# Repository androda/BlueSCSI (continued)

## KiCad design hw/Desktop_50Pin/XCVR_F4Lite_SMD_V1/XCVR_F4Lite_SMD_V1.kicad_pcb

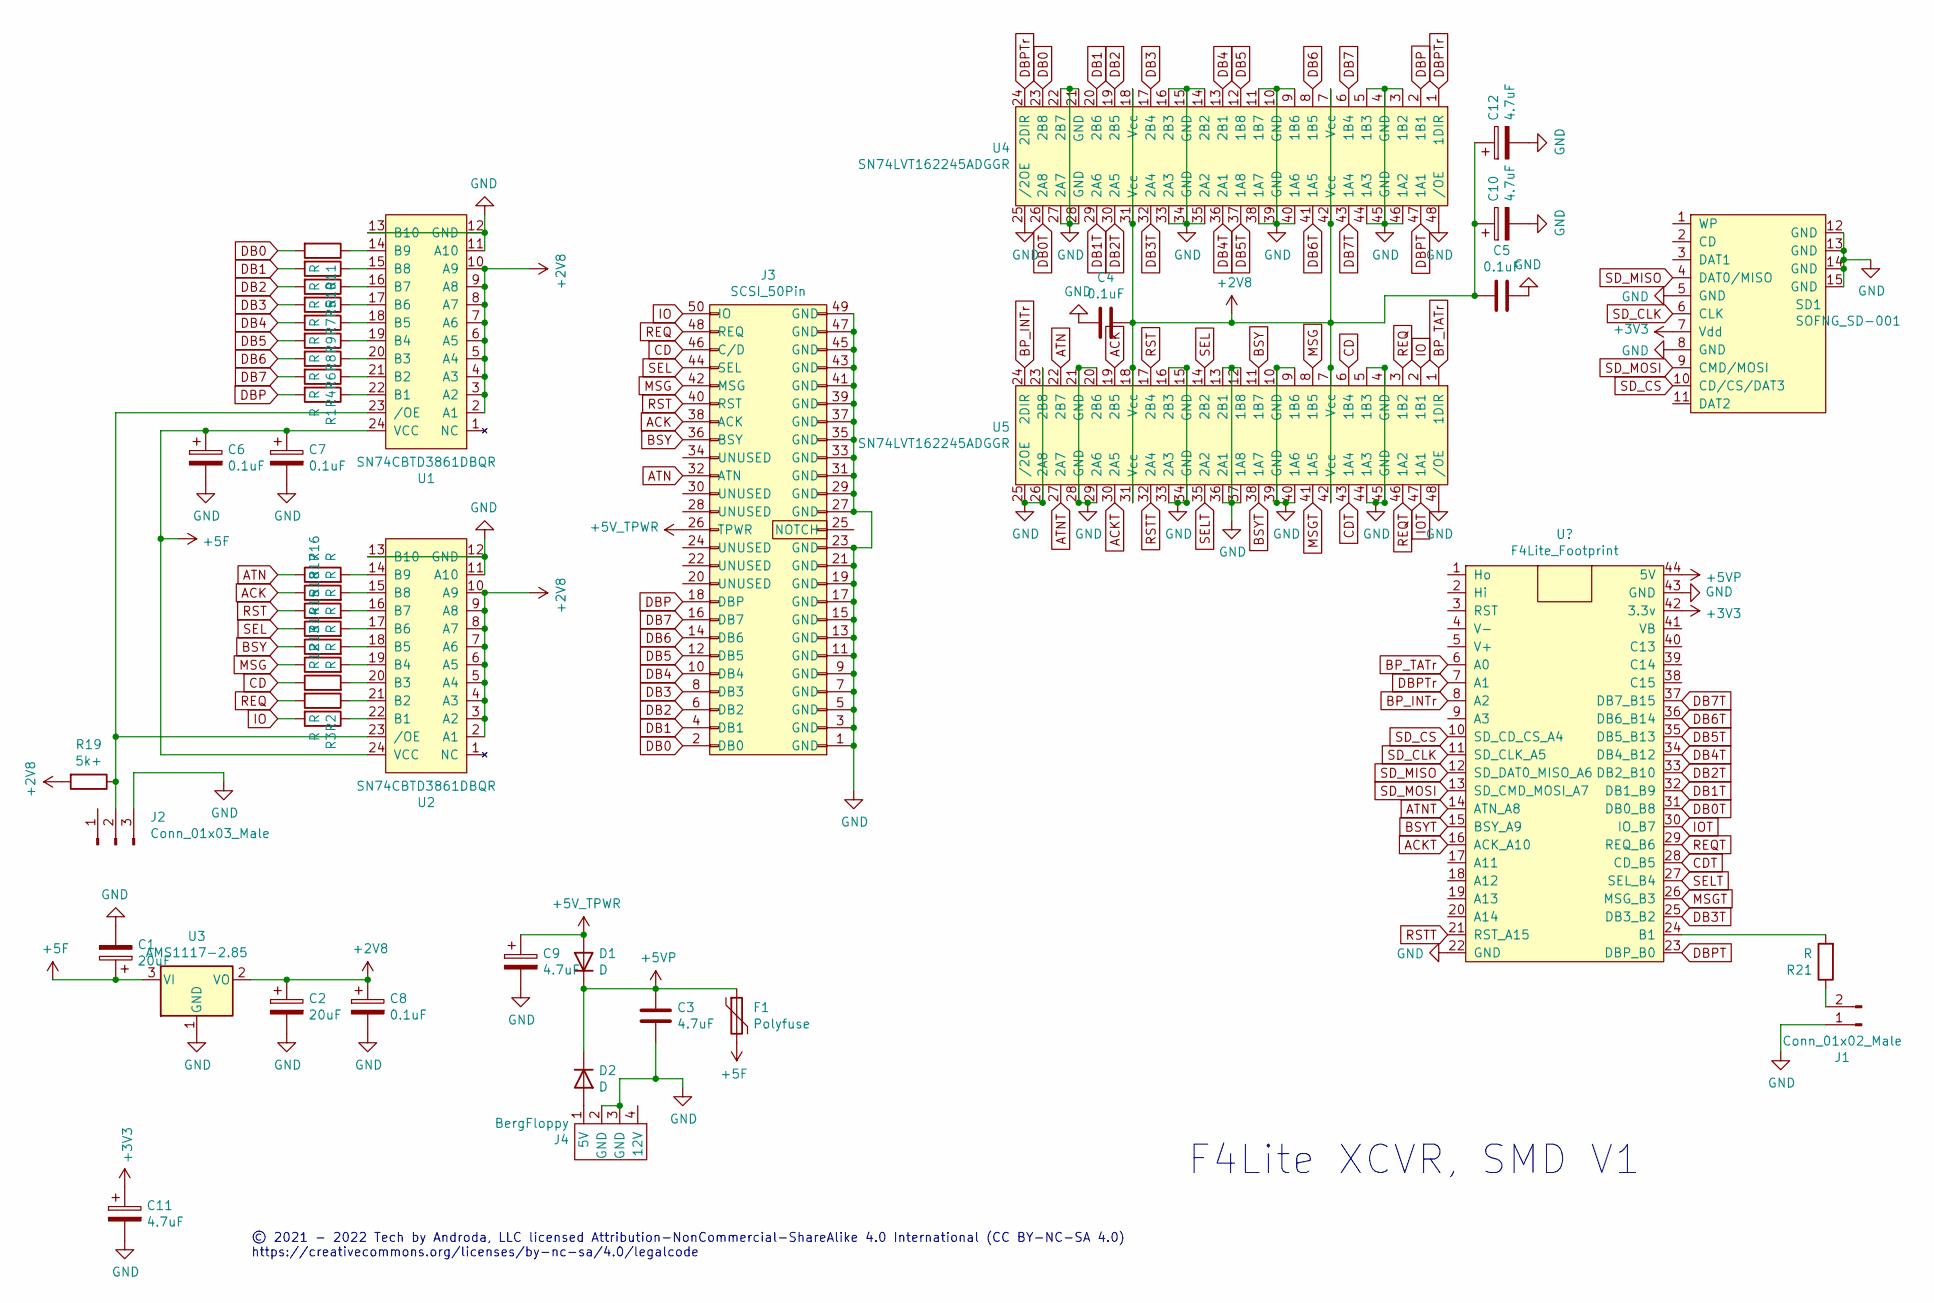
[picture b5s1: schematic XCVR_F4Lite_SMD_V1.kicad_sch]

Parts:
C1, C2: 20uF; C_1206_3216Metric_Pad1.42x1.75mm_HandSolder
C3, C9, C10, C11, C12: 4.7uF; C_0805_2012Metric_Pad1.15x1.40mm_HandSolder
C4, C5, C6, C7, C8: 0.1uF; C_0805_2012Metric_Pad1.15x1.40mm_HandSolder
D1, D2: D; D_SMA
F1: Polyfuse; Fuse_BelFuse_0ZRE0005FF_L8.3mm_W3.8mm
J1: Conn_01x02_Male; PinHeader_1x02_P2.54mm_Vertical
J2: Conn_01x03_Male; PinHeader_1x03_P2.54mm_Vertical
J3: SCSI_50Pin; SCSI50_EdgeConn
J4: BergFloppy; BergFloppy_RightAngle
R1, R2, R3, R4, R5, R6, R7, R8, R9, R10, R11, R12, R13, R14, R15, R16, R17, R18: R; R_0603_1608Metric_Pad1.05x0.95mm_HandSolder
R19: 5k+; R_0805_2012Metric_Pad1.15x1.40mm_HandSolder
R21: R; R_0805_2012Metric_Pad1.15x1.40mm_HandSolder
SD1: SOFNG_SD-001
U1, U2: SN74CBTD3861DBQR; SSOP-24_3.9x8.7mm_P0.635mm
U3: AMS1117-2.85; SOT-223-3_TabPin2
U4, U5: SN74LVT162245ADGGR; TSSOP-48_6.1x12.5mm_P0.5mm

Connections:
+2V8: C2.1, C4.1, C5.1, C8.1, C10.1, C12.1, R19.2, U1.2 (A1), U1.3 (A2), U1.4 (A3), U1.5 (A4), U1.6 (A5), U1.7 (A6), U1.8 (A7), U1.9 (A8), U1.10 (A9), U2.2 (A1), U2.3 (A2), U2.4 (A3), U2.5 (A4), U2.6 (A5), U2.7 (A6), U2.8 (A7), U2.9 (A8), U2.10 (A9), U3.2 (VO), U4.7 (Vcc), U4.18 (Vcc), U4.31 (Vcc), U4.42 (Vcc), U5.7 (Vcc), U5.18 (Vcc), U5.31 (Vcc), U5.42 (Vcc)
+3V3: C11.1, SD1.7 (Vdd); also elsewhere on the board
+5F: C1.1, C6.1, C7.1, F1.2, U1.24 (VCC), U2.24 (VCC), U3.3 (VI)
+5V: C9.1, D1.2 (A), J3.26 (TPWR)
+5VP: C3.1, D1.1 (K), D2.1 (K), F1.1; also elsewhere on the board
ACK: J3.38 (ACK), R17.1, U5.19 (2B5)
ACKT: U5.30 (2A5); also elsewhere on the board
ATN: J3.32 (ATN), R16.1, U5.22 (2B7)
ATNT: U5.27 (2A7); also elsewhere on the board
BP_INTr: U5.24 (2DIR); also elsewhere on the board
BP_TATr: U5.1 (1DIR); also elsewhere on the board
BSY: J3.36 (BSY), R14.1, U5.11 (1B7)
BSYT: U5.38 (1A7); also elsewhere on the board
CD: J3.46 (C/D), R12.1, U5.6 (1B4)
CDT: U5.43 (1A4); also elsewhere on the board
DB0: J3.2 (DB0), R11.2, U4.23 (2B8)
DB0T: U4.26 (2A8); also elsewhere on the board
DB1: J3.4 (DB1), R10.2, U4.20 (2B6)
DB1T: U4.29 (2A6); also elsewhere on the board
DB2: J3.6 (DB2), R5.2, U4.19 (2B5)
DB2T: U4.30 (2A5); also elsewhere on the board
DB3: J3.8 (DB3), R7.2, U4.17 (2B4)
DB3T: U4.32 (2A4); also elsewhere on the board
DB4: J3.10 (DB4), R9.2, U4.13 (2B1)
DB4T: U4.36 (2A1); also elsewhere on the board
DB5: J3.12 (DB5), R8.2, U4.12 (1B8)
DB5T: U4.37 (1A8); also elsewhere on the board
DB6: J3.14 (DB6), R6.2, U4.8 (1B5)
DB6T: U4.41 (1A5); also elsewhere on the board
DB7: J3.16 (DB7), R4.2, U4.6 (1B4)
DB7T: U4.43 (1A4); also elsewhere on the board
DBP: J3.18 (DBP), R1.2, U4.2 (1B1)
DBPT: U4.47 (1A1); also elsewhere on the board
DBPTr: U4.1 (1DIR), U4.24 (2DIR); also elsewhere on the board
GND: C1.2, C2.2, C3.2, C4.2, C5.2, C6.2, C7.2, C8.2, C9.2, C10.2, C11.2, C12.2, J1.1, J2.3, J3.1 (GND), J3.3 (GND), J3.5 (GND), J3.7 (GND), J3.9 (GND), J3.11 (GND), J3.13 (GND), J3.15 (GND), J3.17 (GND), J3.19 (GND), J3.21 (GND), J3.23 (GND), J3.27 (GND), J3.29 (GND), J3.31 (GND), J3.33 (GND), J3.35 (GND), J3.37 (GND), J3.39 (GND), J3.41 (GND), J3.43 (GND), J3.45 (GND), J3.47 (GND), J3.49 (GND), J4.2 (GND), J4.3 (GND), SD1.5 (GND), SD1.8 (GND), SD1.12 (GND), SD1.13 (GND), SD1.14 (GND), SD1.15 (GND), U1.11 (A10), U1.12 (GND), U1.13 (B10), U2.11 (A10), U2.12 (GND), U2.13 (B10), U3.1 (GND), U4.3 (1B2), U4.4 (GND), U4.5 (1B3), U4.9 (1B6), U4.10 (GND), U4.11 (1B7), U4.14 (2B2), U4.15 (GND), U4.16 (2B3), U4.21 (GND), U4.22 (2B7), U4.25 (/2OE), U4.27 (2A7), U4.28 (GND), U4.33 (2A3), U4.34 (GND), U4.35 (2A2), U4.38 (1A7), U4.39 (GND), U4.40 (1A6), U4.44 (1A3), U4.45 (GND), U4.46 (1A2), U4.48 (/OE), U5.4 (GND), U5.5 (1B3), U5.9 (1B6), U5.10 (GND), U5.12 (1B8), U5.13 (2B1), U5.15 (GND), U5.16 (2B3), U5.20 (2B6), U5.21 (GND), U5.23 (2B8), U5.25 (/2OE), U5.26 (2A8), U5.28 (GND), U5.29 (2A6), U5.33 (2A3), U5.34 (GND), U5.36 (2A1), U5.37 (1A8), U5.39 (GND), U5.40 (1A6), U5.44 (1A3), U5.45 (GND), U5.48 (/OE); also elsewhere on the board
IO: J3.50 (IO), R3.2, U5.2 (1B1)
IOT: U5.47 (1A1); also elsewhere on the board
MSG: J3.42 (MSG), R13.1, U5.8 (1B5)
MSGT: U5.41 (1A5); also elsewhere on the board
unnamed: D2.2 (A), J4.1 (5V)
unnamed: J1.2, R21.1
unnamed: J2.2, R19.1, U1.23 (/OE), U2.23 (/OE)
unnamed: R1.1, U1.22 (B1)
unnamed: R2.1, U2.21 (B2)
unnamed: R3.1, U2.22 (B1)
unnamed: R4.1, U1.21 (B2)
unnamed: R5.1, U1.16 (B7)
unnamed: R6.1, U1.20 (B3)
unnamed: R7.1, U1.17 (B6)
unnamed: R8.1, U1.19 (B4)
unnamed: R9.1, U1.18 (B5)
unnamed: R10.1, U1.15 (B8)
unnamed: R11.1, U1.14 (B9)
unnamed: R12.2, U2.20 (B3)
unnamed: R13.2, U2.19 (B4)
unnamed: R14.2, U2.18 (B5)
unnamed: R15.2, U2.17 (B6)
unnamed: R16.2, U2.14 (B9)
unnamed: R17.2, U2.15 (B8)
unnamed: R18.2, U2.16 (B7)
unnamed 69: R21.2; also elsewhere on the board
REQ: J3.48 (REQ), R2.2, U5.3 (1B2)
REQT: U5.46 (1A2); also elsewhere on the board
RST: J3.40 (RST), R18.1, U5.17 (2B4)
RSTT: U5.32 (2A4); also elsewhere on the board
SD_CLK: SD1.6 (CLK); also elsewhere on the board
SD_CS: SD1.10 (CD/CS/DAT3); also elsewhere on the board
SD_MISO: SD1.4 (DAT0/MISO); also elsewhere on the board
SD_MOSI: SD1.9 (CMD/MOSI); also elsewhere on the board
SEL: J3.44 (SEL), R15.1, U5.14 (2B2)
SELT: U5.35 (2A2); also elsewhere on the board

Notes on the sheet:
© 2021 - 2022 Tech by Androda, LLC licensed Attribution-NonCommercial-ShareAlike 4.0 International (CC BY-NC-SA 4.0) https://creativecommons.org/licenses/by-nc-sa/4.0/legalcode
F4Lite XCVR, SMD V1

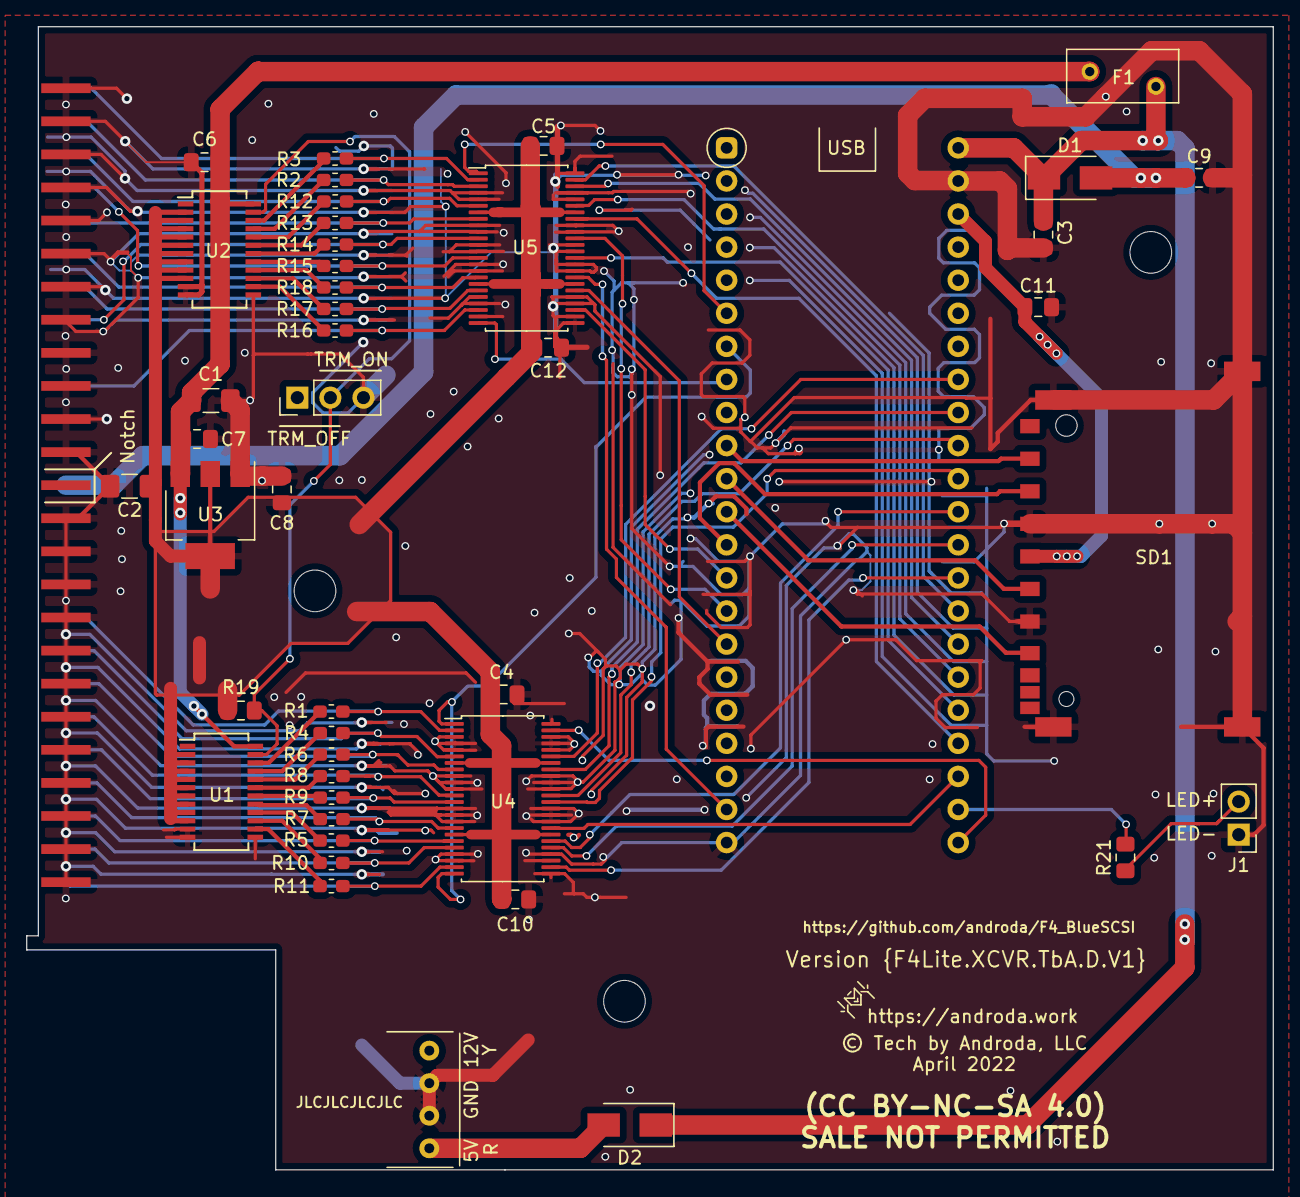
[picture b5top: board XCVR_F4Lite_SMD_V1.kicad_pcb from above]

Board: 2 copper layers, 95.7 x 87.8 mm, 46 parts (0 on the bottom side), 71 nets.

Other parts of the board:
U6: GreenSCSI_F401

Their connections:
+3V3: U6.42; also elsewhere on the board
+5VP: U6.44; also elsewhere on the board
ACKT: U6.16; also elsewhere on the board
ATNT: U6.14; also elsewhere on the board
BP_INTr: U6.8; also elsewhere on the board
BP_TATr: U6.6; also elsewhere on the board
BSYT: U6.15; also elsewhere on the board
CDT: U6.28; also elsewhere on the board
DB0T: U6.31; also elsewhere on the board
DB1T: U6.32; also elsewhere on the board
DB2T: U6.33; also elsewhere on the board
DB3T: U6.25; also elsewhere on the board
DB4T: U6.34; also elsewhere on the board
DB5T: U6.35; also elsewhere on the board
DB6T: U6.36; also elsewhere on the board
DB7T: U6.37; also elsewhere on the board
DBPT: U6.23; also elsewhere on the board
DBPTr: U6.7; also elsewhere on the board
GND: U6.22, U6.43; also elsewhere on the board
IOT: U6.30; also elsewhere on the board
MSGT: U6.26; also elsewhere on the board
unnamed 69: U6.24; also elsewhere on the board
REQT: U6.29; also elsewhere on the board
RSTT: U6.21; also elsewhere on the board
SD_CLK: U6.11; also elsewhere on the board
SD_CS: U6.10; also elsewhere on the board
SD_MISO: U6.12; also elsewhere on the board
SD_MOSI: U6.13; also elsewhere on the board
SELT: U6.27; also elsewhere on the board

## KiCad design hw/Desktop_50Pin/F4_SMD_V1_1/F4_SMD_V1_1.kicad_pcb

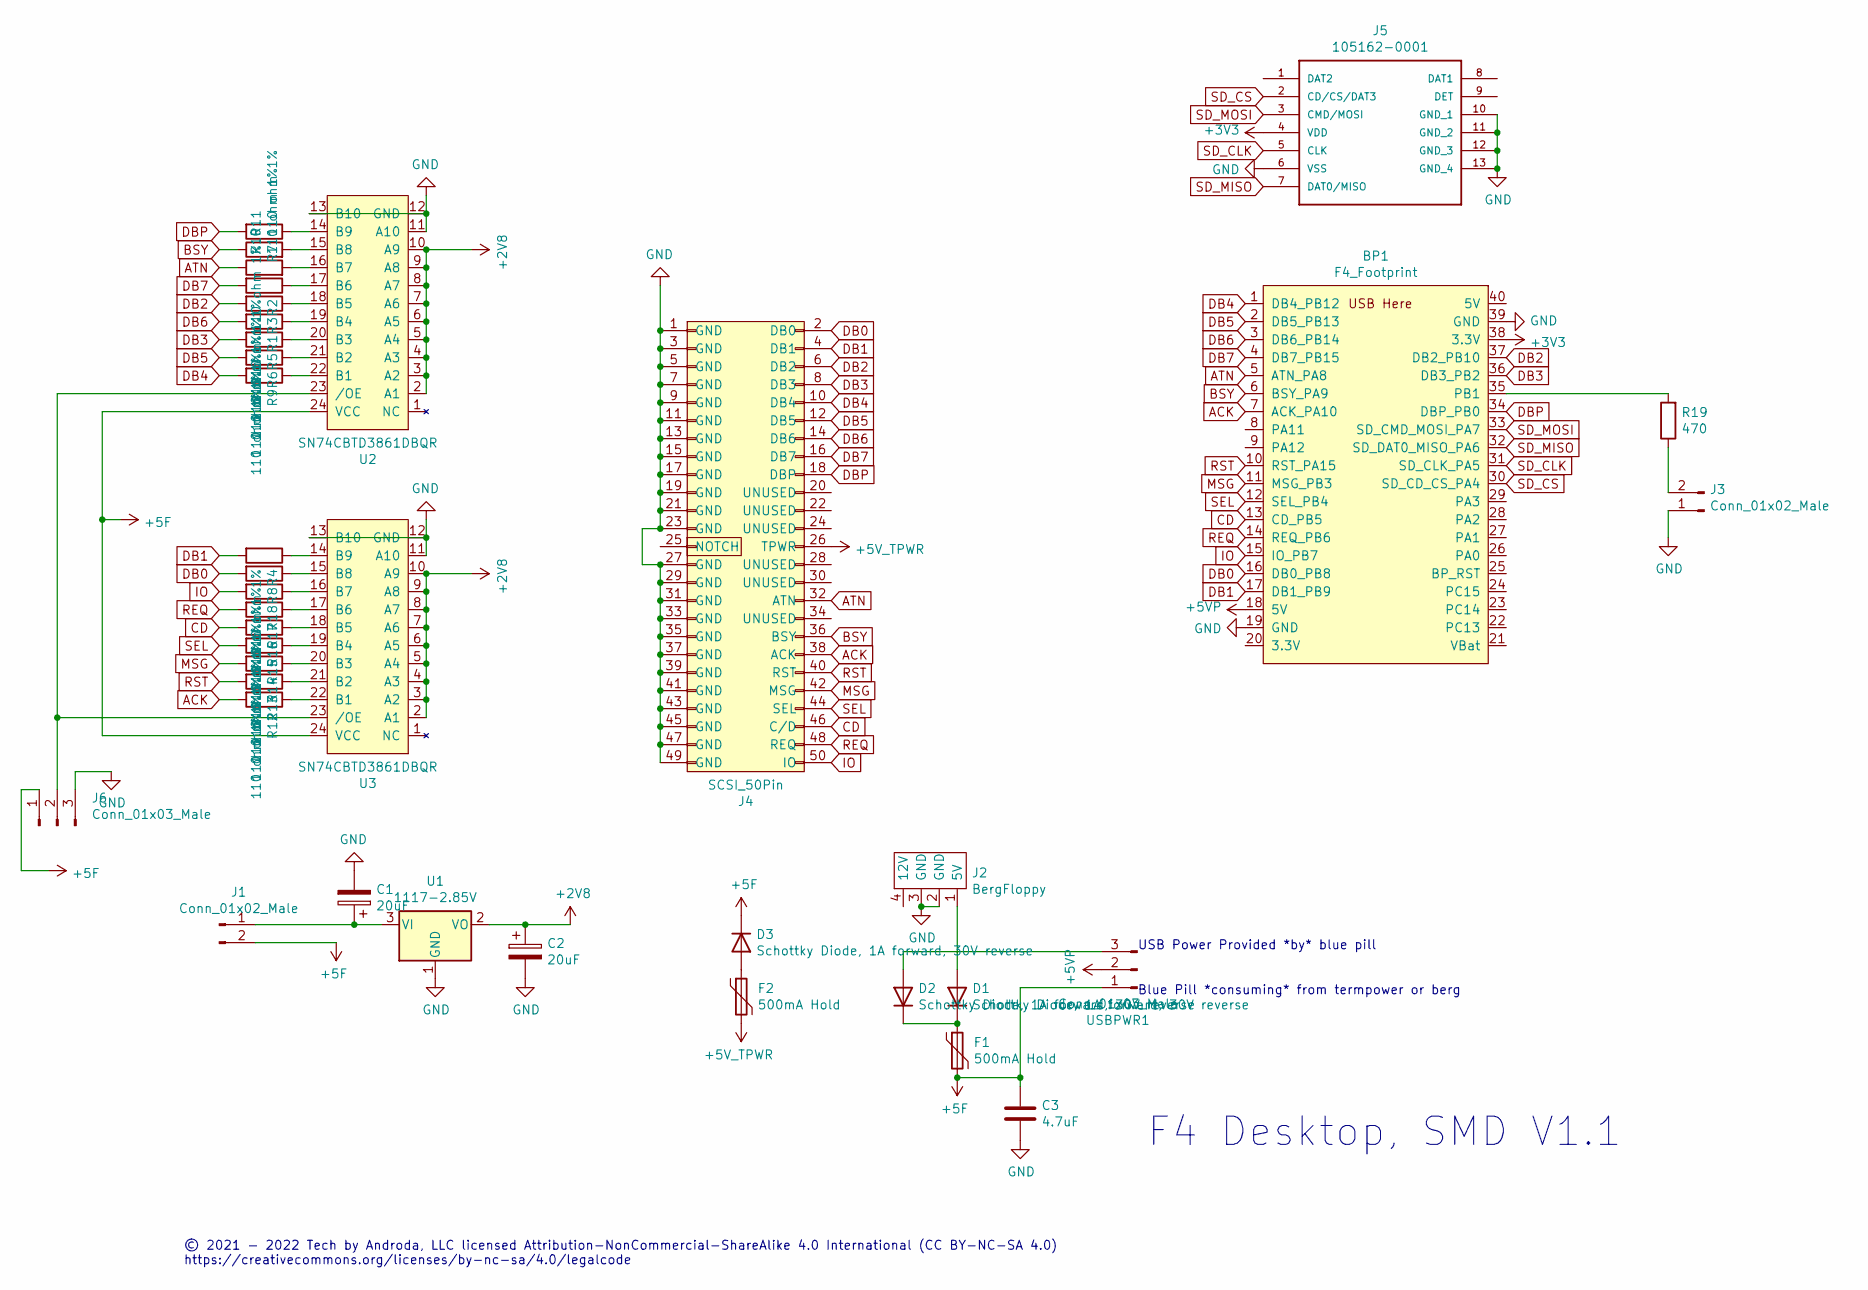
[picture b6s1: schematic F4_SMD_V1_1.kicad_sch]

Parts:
BP1: F4_Footprint; BluePillModule
C1, C2: 20uF; C_1206_3216Metric_Pad1.42x1.75mm_HandSolder
C3: 4.7uF; C_0805_2012Metric_Pad1.15x1.40mm_HandSolder
D1, D2, D3: Schottky Diode, 1A forward, 30V reverse; D_SOD-123F
F1, F2: 500mA Hold; Fuse_0805_2012Metric_Castellated
J1, J3: Conn_01x02_Male; PinHeader_1x02_P2.54mm_Vertical
J2: BergFloppy; BergFloppy_RightAngle
J4: SCSI_50Pin; SCSI_Internal_50Pin
J5: 105162-0001; microsd_molex_1051620001; MANUFACTURER_PART_NUMBER 105162-0001; MOUSER_PART_NUMBER 538-105162-0001
J6: Conn_01x03_Male; PinHeader_1x03_P2.54mm_Vertical
R1, R2, R3, R4, R5, R6, R7, R8, R9, R10, R11, R12, R13, R14, R15, R16, R17, R18: 110 ohm 1%; R_0603_1608Metric_Pad1.05x0.95mm_HandSolder
R19: 470; R_Axial_DIN0207_L6.3mm_D2.5mm_P7.62mm_Horizontal
U1: 1117-2.85V; SOT-223-3_TabPin2
U2, U3: SN74CBTD3861DBQR; SSOP-24_3.9x8.7mm_P0.635mm
USBPWR1: Conn_01x03_Male; PinHeader_1x03_P2.54mm_Vertical

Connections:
+2V8: C2.1, U1.2 (VO), U2.2 (A1), U2.3 (A2), U2.4 (A3), U2.5 (A4), U2.6 (A5), U2.7 (A6), U2.8 (A7), U2.9 (A8), U2.10 (A9), U3.2 (A1), U3.3 (A2), U3.4 (A3), U3.5 (A4), U3.6 (A5), U3.7 (A6), U3.8 (A7), U3.9 (A8), U3.10 (A9)
+3V3: BP1.38 (3.3V), J5.4 (VDD)
+5F: C3.1, D3.1 (K), F1.2, J1.2, J6.1, U2.24 (VCC), U3.24 (VCC), USBPWR1.1; also elsewhere on the board
+5V: F2.2, J4.26 (TPWR)
+5VP: BP1.18 (5V), USBPWR1.2; also elsewhere on the board
ACK: BP1.7 (ACK_PA10), J4.38 (ACK), R12.2
ATN: BP1.5 (ATN_PA8), J4.32 (ATN), R10.1
BSY: BP1.6 (BSY_PA9), J4.36 (BSY), R11.1
CD: BP1.13 (CD_PB5), J4.46 (C/D), R16.2
DB0: BP1.16 (DB0_PB8), J4.2 (DB0), R8.2
DB1: BP1.17 (DB1_PB9), J4.4 (DB1), R4.2
DB2: BP1.37 (DB2_PB10), J4.6 (DB2), R3.2
DB3: BP1.36 (DB3_PB2), J4.8 (DB3), R5.2
DB4: BP1.1 (DB4_PB12), J4.10 (DB4), R9.2
DB5: BP1.2 (DB5_PB13), J4.12 (DB5), R6.2
DB6: BP1.3 (DB6_PB14), J4.14 (DB6), R1.2
DB7: BP1.4 (DB7_PB15), J4.16 (DB7), R2.2
DBP: BP1.34 (DBP_PB0), J4.18 (DBP), R7.2
GND: BP1.19 (GND), BP1.39 (GND), C1.2, C2.2, C3.2, J2.2 (GND), J2.3 (GND), J3.1, J4.1 (GND), J4.3 (GND), J4.5 (GND), J4.7 (GND), J4.9 (GND), J4.11 (GND), J4.13 (GND), J4.15 (GND), J4.17 (GND), J4.19 (GND), J4.21 (GND), J4.23 (GND), J4.27 (GND), J4.29 (GND), J4.31 (GND), J4.33 (GND), J4.35 (GND), J4.37 (GND), J4.39 (GND), J4.41 (GND), J4.43 (GND), J4.45 (GND), J4.47 (GND), J4.49 (GND), J5.6 (VSS), J5.10 (GND_1), J5.11 (GND_2), J5.12 (GND_3), J5.13 (GND_4), J6.3, U1.1 (GND), U2.11 (A10), U2.12 (GND), U2.13 (B10), U3.11 (A10), U3.12 (GND), U3.13 (B10)
IO: BP1.15 (IO_PB7), J4.50 (IO), R18.2
MSG: BP1.11 (MSG_PB3), J4.42 (MSG), R14.2
unnamed: BP1.35 (PB1), R19.2
unnamed: C1.1, J1.1, U1.3 (VI)
unnamed: D1.1 (K), D2.1 (K), F1.1
unnamed: D1.2 (A), J2.1 (5V)
unnamed 25: D2.2 (A), USBPWR1.3; also elsewhere on the board
unnamed: D3.2 (A), F2.1
unnamed: J3.2, R19.1
unnamed: J6.2, U2.23 (/OE), U3.23 (/OE)
unnamed: R1.1, U2.19 (B4)
unnamed: R2.1, U2.17 (B6)
unnamed: R3.1, U2.18 (B5)
unnamed: R4.1, U3.14 (B9)
unnamed: R5.1, U2.20 (B3)
unnamed: R6.1, U2.21 (B2)
unnamed: R7.1, U2.14 (B9)
unnamed: R8.1, U3.15 (B8)
unnamed: R9.1, U2.22 (B1)
unnamed: R10.2, U2.16 (B7)
unnamed: R11.2, U2.15 (B8)
unnamed: R12.1, U3.22 (B1)
unnamed: R13.1, U3.21 (B2)
unnamed: R14.1, U3.20 (B3)
unnamed: R15.1, U3.19 (B4)
unnamed: R16.1, U3.18 (B5)
unnamed: R17.1, U3.17 (B6)
unnamed: R18.1, U3.16 (B7)
REQ: BP1.14 (REQ_PB6), J4.48 (REQ), R17.2
RST: BP1.10 (RST_PA15), J4.40 (RST), R13.2
SD_CLK: BP1.31 (SD_CLK_PA5), J5.5 (CLK)
SD_CS: BP1.30 (SD_CD_CS_PA4), J5.2 (CD/CS/DAT3)
SD_MISO: BP1.32 (SD_DAT0_MISO_PA6), J5.7 (DAT0/MISO)
SD_MOSI: BP1.33 (SD_CMD_MOSI_PA7), J5.3 (CMD/MOSI)
SEL: BP1.12 (SEL_PB4), J4.44 (SEL), R15.2

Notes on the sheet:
© 2021 - 2022 Tech by Androda, LLC licensed Attribution-NonCommercial-ShareAlike 4.0 International (CC BY-NC-SA 4.0) https://creativecommons.org/licenses/by-nc-sa/4.0/legalcode
F4 Desktop, SMD V1.1
Blue Pill *consuming* from termpower or berg
USB Power Provided *by* blue pill

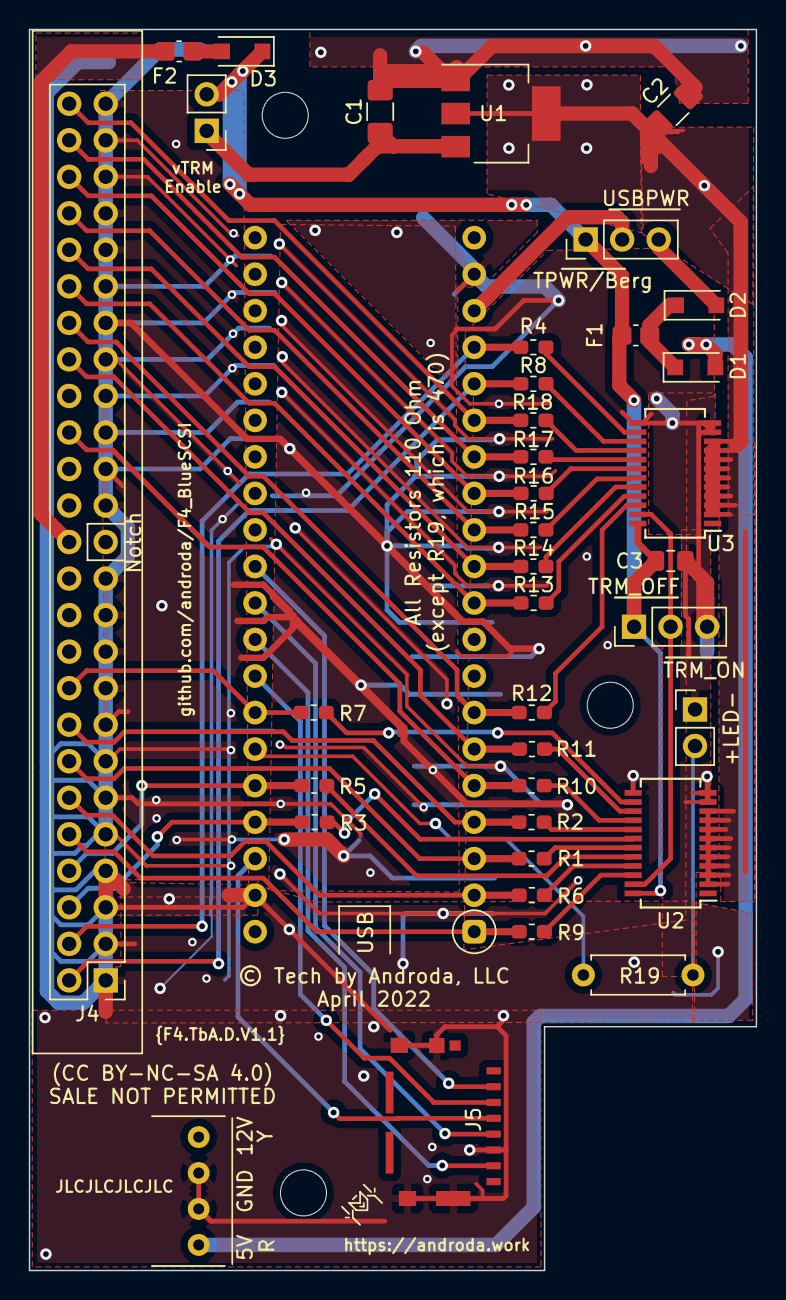
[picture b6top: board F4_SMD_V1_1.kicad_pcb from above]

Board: 2 copper layers, 50.5 x 86.3 mm, 38 parts (0 on the bottom side), 54 nets.

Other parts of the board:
USBPWR: Conn_01x03_Male; PinHeader_1x03_P2.54mm_Vertical

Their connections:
+5F: USBPWR.1; also elsewhere on the board
+5VP: USBPWR.2; also elsewhere on the board
unnamed 25: USBPWR.3; also elsewhere on the board

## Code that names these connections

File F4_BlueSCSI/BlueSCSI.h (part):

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//#define DB5       PB13    // SCSI:DB5
//#define DB6       PB14    // SCSI:DB6
//#define DB7       PB15    // SCSI:DB7
//#define DBP       PB0     // SCSI:DBP

#define ATN       PA8      // SCSI:ATN
#define BSY       PA9      // SCSI:BSY
#define ACK       PA10     // SCSI:ACK
#define RST       PA15     // SCSI:RST
#define MSG       PB3      // SCSI:MSG
#define SEL       PB4      // SCSI:SEL
#define CD        PB5      // SCSI:C/D
#define REQ       PB6      // SCSI:REQ
#define IO        PB7      // SCSI:I/O

#define LED       PC13     // LED
#define LED2      PB1      // Driven LED

// Image Set Selector
#define IMAGE_SELECT1   PC14
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#define GPIOREG(VPIN)     ((VPIN) >= 16 ? PBREG : PAREG)
#define BITMASK(VPIN)     (1 << ((VPIN) & 15))

#define vATN       PA(8)      // SCSI:ATN
#define vBSY       PA(9)      // SCSI:BSY
#define vACK       PA(10)     // SCSI:ACK
#define vRST       PA(15)     // SCSI:RST
#define vMSG       PB(3)      // SCSI:MSG
#define vSEL       PB(4)      // SCSI:SEL
#define vCD        PB(5)      // SCSI:C/D
#define vREQ       PB(6)      // SCSI:REQ
#define vIO        PB(7)      // SCSI:I/O
#define vSD_CS     PA(4)      // SDCARD:CS

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#else

// Turn on the output only for BSY
#define SCSI_BSY_ACTIVE()      { pinMode(BSY, OUTPUT_OPEN_DRAIN); SCSI_OUT(vBSY,  active) }

// BSY,REQ,MSG,CD,IO Turn off output, BSY is the last input
#define SCSI_TARGET_INACTIVE() { SCSI_OUT(vREQ,inactive); SCSI_PHASE_CHANGE(SCSI_PHASE_DATAOUT); SCSI_OUT(vBSY,inactive); pinMode(BSY, INPUT); }

// BSY,REQ,MSG,CD,IO Turn on the output (no change required for OD)
#define SCSI_TARGET_ACTIVE()   { }
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*/
/**
 * BSRR register generator
 * Totally configurable for which pin is each data bit, which pin is PTY, and which pin is REQ.
 * The only requirement is that data and parity pins are in the same GPIO block.
 * REQ can be specified as -1 to ignore, as it doesn't have to be in the same GPIO block.
 * This is dramatically slower than the original static array, but is easier to configure
 */
static uint32_t genBSRR(uint32_t data) {
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  }

  // BSRR set REQ if specified
  // Only set > 0 if it's in the same GPIO block as DB and DBP
  if (reqPosition >= 0) {
    output |= 0x01 << reqPosition;
  }
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
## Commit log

2021-11-11 Remove parent bluescsi files
2021-11-11 Move and rename, update readme
2021-11-11 Add to LICENSE
2022-02-22 Allow for 2048 block size
2022-02-22 Fix warnings
2022-02-22 Dont consider LUN in filename as it wont work, just force to 0
2022-02-22 Various fixes for VAXstation
2022-02-22 Fix indenting
2022-02-22 Minor white space fixes. Snapshot to VERSION
2022-03-05 Fighting with markdown
2022-03-05 Update README
    generally generally
2022-03-05 Update Readme
    Link to flashing firmware updates wiki page
2022-03-21 Add SGI Indy Benchmark Results
2022-04-06 Make documentation license a little clearer
2022-04-06 More docs license
    Maybe overboard to stick it everywhere, but why not?
2022-04-06 Build Instructions
    Not absolutely the clearest, but it's all laid out at least
2022-04-06 Doc tweaks
2022-04-06 Update Hardware License
2022-04-06 Hardware Release, in KiCAD V6 format
    CC BY-NC-SA 4.0 licensed hardware release.
    Note that these are all slightly tweaked versions of the ones currently for sale, and as such have not been produced for testing.
2022-04-07 Fix documentation flub
2022-04-07 Fix filename
    Not sure where this came from, that filename is from an ancient prototype
2022-04-07 Pointer to dev instructions folder
2022-04-07 CLZ optimization
2022-04-07 Optimize handling of reset interrupt.
2022-04-07 F4-specific fix for EXTI issues
2022-04-07 Add explicit "bx lr" to longjmpFromInterrupt.
2022-04-07 Move the db_bsrr table to RAM for faster performance.
2022-04-07 Separate out writeDataLoop. Adjust the timing, and incorporate the loop overhead in to one of the desired delays.
2022-04-07 Read timing adjustment, now getting 1216 KB/sec on LC III+. First pass at write speed optimization, now getting 825 KB/sec on LC III+. Whitespace cleanup.
2022-04-07 Pin down alignment for writeDataLoop and readDataLoop, and perform some additional timing adjustment.
2022-04-07 Switch to latest toolchain. Tune the timing for the readDataLoop with the latest toolchain.
2022-04-07 Change readDataLoop alignment to 16
2022-04-07 F4-specific changes
    No BRR, and readout is different
2022-04-07 Missed this, another F4 specific difference
2022-04-07 Try clock speeds from 50 -> 32mhz for SD communication Helps compatibility with SD and different STM32 chips. Add warning if under 40mhz - testing showed 40-50mhz gave almost no change in speed
    Thanks @marcelv-3 via https://github.com/erichelgeson/BlueSCSI/discussions/58
2022-04-07 F4-specific tweaks to SD setup
2022-04-07 Merge pull request #71 from mactcp/AppleHDSCSetup
    Apple HD SC Setup support
2022-04-07 Image set selection
2022-04-07 Use PC pins for image select since F4 uses PB1 already
2022-04-07 Reorder bus phase change and file.seek() so that file.seek() acts as a bus settle delay.
2022-04-07 Correct == to = for verify with bytchk of 3
2022-04-07 Remove obsolete initialization of sector data overrun byte.
2022-04-07 init blk1 Thanks to @moof via discord
2022-04-07 Update snapshot version
2022-04-15 Squashed commit of the following:
    commit 76483ff815e1e442cda9677f54d5c8be8428723f
    Author: androda <androda@users.noreply.github.com>
    Date: Fri Apr 15 06:45:37 2022 -0600
    Add HW
    commit 6bc545ae7fe749063ec50225f4415f7c3cb96f44
    Author: androda <androda@users.noreply.github.com>
2022-04-15 Update snapshot date due to merge
2022-04-19 F4Lite THT V1.1
    Creative Commons Non-Commercial Licensed Version 1.1 of the F4Lite Desktop Design
2022-05-03 Support for images larger than 4GB
2022-05-03 Add version note for when xcvr is turned on
2022-05-03 Remove unused SCSI_SELECT - upstream has moved to a different approch to support PC98/etc
2022-05-03 Replace magic numbers with constants - thanks Jokker
2022-05-03 Implement Test Unit Ready command
2022-05-03 Add back LUN filename parsing
2022-05-03 Remove unused settings as we always use the OPTIMISEd ones
2022-05-03 Cleanup of SCSI phase change code, and adjustment of bus settle delays.
2022-05-03 Tweaks after merging to get build working
2022-05-13 Change snapshot version to today's date
2022-06-01 Remove the usage of String, saves quite a bit of flash
2022-06-01 Fix issue where log file would close when logging was enabled. Thanks @marcelv-3 https://github.com/erichelgeson/BlueSCSI/discussions/103#discussioncomment-2779471
2022-06-01 Add sd card volume format to log.txt
2022-06-01 Remove tabs
2022-06-01 Merge pull request #114 from erichelgeson/eric/newCmds
    Four new commands & some Sense
2022-06-01 Merge pull request #116 from erichelgeson/eric/noopCmds
    Add cmds that are ok to respond GOOD and not do anything.
2022-06-01 Merge pull request #117 from erichelgeson/eric/reordercmds
    Move read/write command earlier, few kb/sec faster read/write
2022-06-19 Move TRANSCEIVER_IO_SET out of writeDataLoop. Add matching TRANSCEIVER_IO_SET(vTR_DBP,TR_INPUT) to writeDataPhase() and writeDataPhaseSD()
2022-06-19 Change ifdef for difference between upstream and this fork
2022-06-19 Alignment adjustment to make XCVR perform the same as non-XCVR
2022-06-19 Merge pull request #120 from erichelgeson/eric/readDefectData
    Implement Read Defect Data 0x37
2022-06-19 Merge pull request #115 from mynameistroy/troy/function_table
    Switched to function table for SCSI commands
2022-06-20 Re-Applying F4 Specific Changes
2022-06-21 Debug off
2022-06-21 Merge pull request #122 from erichelgeson/eric/spi
    We only need to test full and half speed spi
2022-06-21 Fix cherry pick
2022-06-21 Wider SD card speed support, and bump snapshot version
2022-06-27 Cleanup some stray command table definitions. Fix handling of dbd bit in onModeSense()
2022-06-27 Merge pull request #134 from erichelgeson/eric/bugfixes
    Fix onReadCapacity calculation & Sense offset for Flexable Geometry
2022-06-27 Merge pull request #135 from mynameistroy/troy/minorfixes
    minor fixes
2022-06-27 Merge pull request #137 from erichelgeson/eric/senseCache0x08
    Add Sense page for caching 0x08
2022-06-27 Merge pull request #138 from erichelgeson/eric/vdrName
    Change product so vendor specific Quantum commands are not issued
2022-06-27 Change snapshot date
    And rename the vendor block
2022-07-01 PowerBook v1.1
    Quality of life change, moved the SD card slot so it's easier to use. Still fits in the standard drive footprint.
2022-07-27 Switch GPIO Modes
    Many of the new F401 dev modules don't seem to work unless they're in push-pull mode. Thus, use open drain for F411 only.
2022-07-27 Update date, and customize log file version string
    Now printing out properly, F4 and F4Lite.
2022-07-28 Back to snapshot
2022-07-28 Merge pull request #140 from mynameistroy/troy/icd
    Support for Atari ST ICD commands
2022-07-28 Merge pull request #141 from mynameistroy/troy/lun_fix
    stop invalid LUNs from reading unallocated structs
2022-07-28 Back to F4 BlueSCSI
2022-07-28 Merge pull request #142 from mynameistroy/troy/phase_fix
    SCSI Phase handling improved for SCSI-2
2022-07-28 LED on/off is around all commands, no need to have it here.
2022-07-28 Fix character count
2022-07-28 DigitalRead here
    gpio_read is not defined in F4
2022-07-28 code layout adjustments
2022-07-28 more code shuffling
2022-07-28 out of phase error fixed, SGI Indy works now
    basic determination of arbitration
2022-07-28 ISO-9660 raw image support for CD/DVD emulation
2022-07-28 merged in latest HEAD, cleaned up some warnings
2022-07-28 added missing set of raw sector size
2022-07-28 alternative sector size supported
    this let's .BIN files get used at the very least, maybe more depending
    on how some of the other optical formats look
    reverted a small SCSI phase change that causes problems
2022-07-28 Re-apply F4 specific changes
2022-07-28 Add picture of qmk_toolbox
2022-07-28 qmk_toolbox showing successful flash
2022-09-20 cleanup Apple Mode Page handling
2022-09-20 minor logging cleanup
2022-09-20 MODE SELECT supports CDROM 512/2048 sector toggle
    CDROM devices return a DBD properly
    CDROM Error Mode Page has a default retry of 1
    More streamlining of debug logging
2022-09-20 Cleaned up MODE_SELECT blocksize request
    OnReadBuffer uses generic buffer and only transfers actual length
2022-09-20 Add apostrophe to log message
2022-09-20 Merge pull request #151 from erichelgeson/eric/longFileNames
    Allow for file names to be up to 64 chars
2022-09-20 Define new string for versioning
2022-09-20 Re-add apostrophe
2022-10-03 Updated designs, more SMD friendly
    Still CC BY-NC-SA 4.0
2022-12-20 Merge pull request #183 from mynameistroy/troy/myst_fix
    Fix for incorrect response to READ_DVD_STRUCTURE
2022-12-20 Merge pull request #194 from mynameistroy/troy/cdb_length_fix
    added a full lookup table for cdb length
2022-12-20 Merge pull request #196 from mynameistroy/troy/megaste_mode
    MegaSTE mode added for using IDs as LUNs
2022-12-20 Merge pull request #201 from erichelgeson/eric/fragmented
    Warn user if file is fragmented
2022-12-20 Change to release version date
2024-03-22 Attempting PIO Build System
